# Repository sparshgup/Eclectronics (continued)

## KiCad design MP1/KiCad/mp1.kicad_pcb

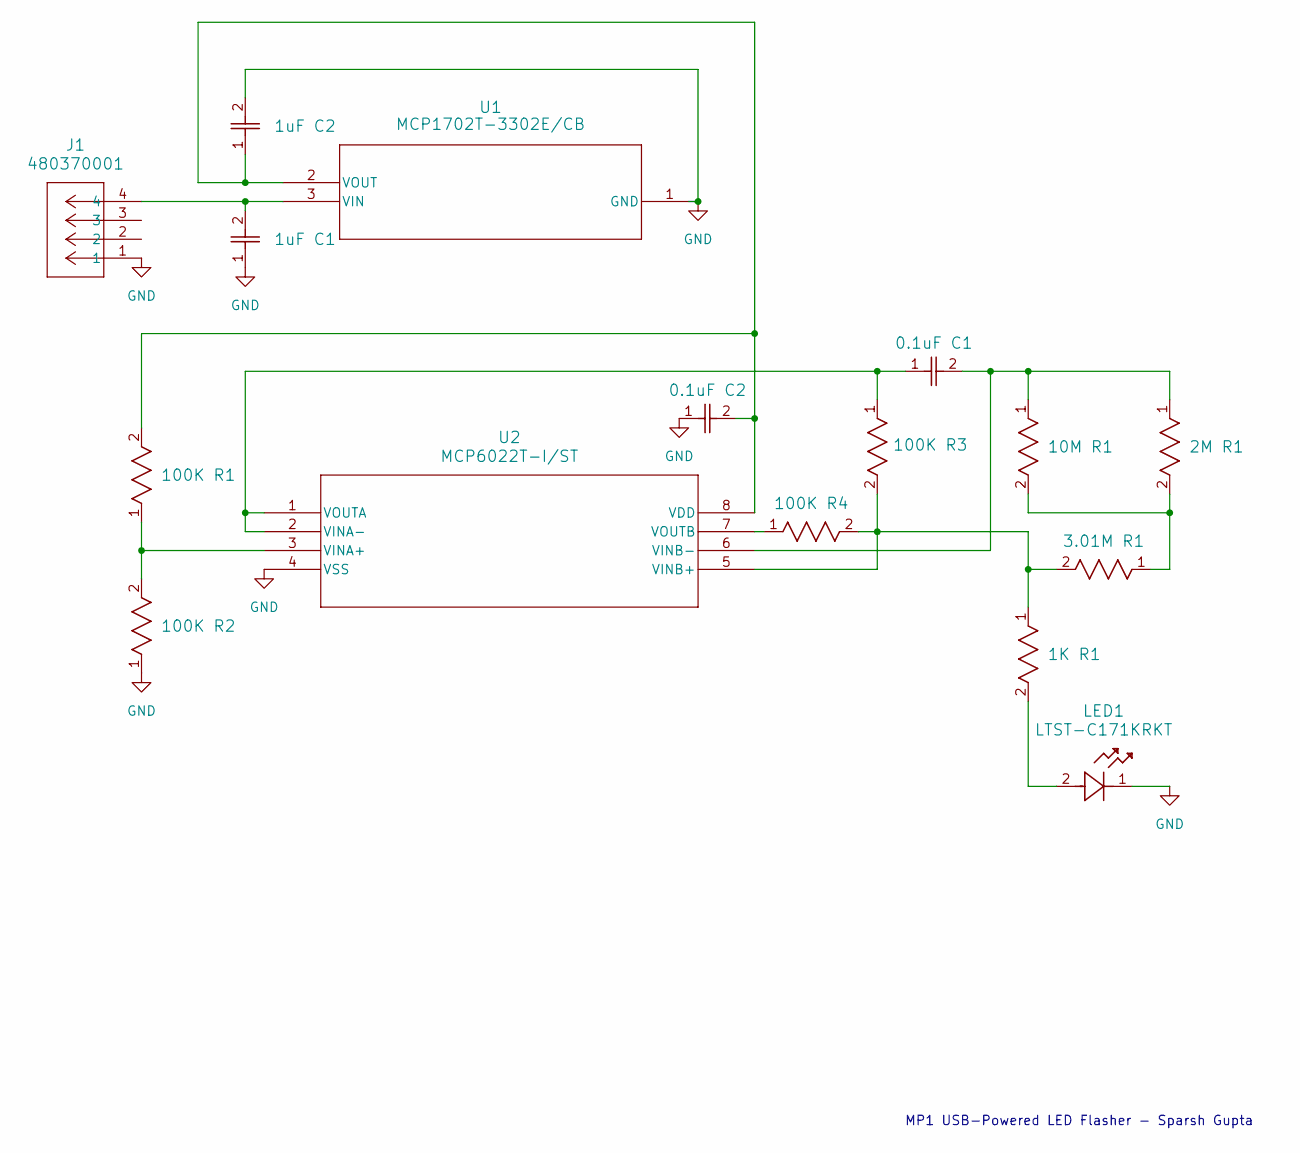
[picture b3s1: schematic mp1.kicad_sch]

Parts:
0.1uF C1, 0.1uF C2: CC0603JRX7R9BB104; CAP_CC0603_YAG
1K R1: RC0603FR-071KL; RC0603N_YAG
1uF C1, 1uF C2: C0603C105K3RACTU; CAPC17595_95N_KEM
2M R1: RC0603FR-072ML; RC0603N_YAG
3.01M R1: RC0603FR-073M01L; RC0603N_YAG
10M R1: RC0603FR-0710ML; RC0603N_YAG
100K R1, 100K R2, 100K R3, 100K R4: RC0603FR-07100KL; RC0603N_YAG
J1: 480370001; CONN_480370001_MOL
LED1: LTST-C171KRKT; LED_LTST-C171_LTO
U1: MCP1702T-3302E/CB; SOT-23A_MC_MCH
U2: MCP6022T-I/ST; TSSOP8_MC_MCH

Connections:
GND: 0.1uF C2.1, 1uF C1.1, 1uF C2.2, 100K R2.1, J1.1, LED1.1, U1.1 (GND), U2.4 (VSS)
unnamed: 1K R1.2, LED1.2
unnamed: 2M R1.2, 3.01M R1.1, 10M R1.2
unnamed: 1uF C1.2, J1.4, U1.3 (VIN)
unnamed: 0.1uF C2.2, 1uF C2.1, 100K R1.2, U1.2 (VOUT), U2.8 (VDD)
unnamed: 100K R1.1, 100K R2.2, U2.3 (VINA+)
unnamed: 0.1uF C1.1, 100K R3.1, U2.1 (VOUTA), U2.2 (VINA-)
unnamed: 1K R1.1, 3.01M R1.2, 100K R3.2, 100K R4.2, U2.5 (VINB+)
unnamed: 0.1uF C1.2, 2M R1.1, 10M R1.1, U2.6 (VINB-)
unnamed: 100K R4.1, U2.7 (VOUTB)

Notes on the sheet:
MP1 USB-Powered LED Flasher - Sparsh Gupta

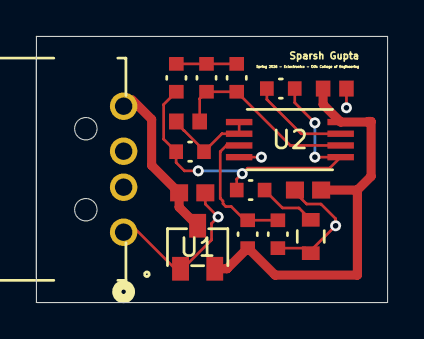
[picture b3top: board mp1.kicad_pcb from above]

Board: 2 copper layers, 19.5 x 14.8 mm, 16 parts (0 on the bottom side), 10 nets.

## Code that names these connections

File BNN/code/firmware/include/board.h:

#pragma once

// Pin map for the BNN board (matches the schematic).

#define PIN_UART_TX        0    // -> FPGA UART_RX (pin 25)
#define PIN_UART_RX        1    // <- FPGA UART_TX (pin 27)

#define PIN_SPI_SCK        2    // shared SPI bus: SCK to FPGA flash + FPGA pin 15
#define PIN_SPI_MOSI       3    // shared: MOSI / FPGA SI (flash DI + FPGA pin 17)
#define PIN_SPI_MISO       4    // shared: MISO / FPGA SO (flash DO + FPGA pin 14)
#define PIN_FPGA_CS        5    // FPGA pin 26 — data SPI CS (also doubles as SS during slave-SPI config)
#define PIN_FLASH_CS       6    // FPGA flash CS (also FPGA pin 16 — SPI_SS during slave-SPI config)
#define PIN_FPGA_CLK       7    // PWM out -> FPGA pin 35 (global buffer)

#define PIN_FPGA_CRESET    8    // -> FPGA CRESET_B (pin 8), active low
#define PIN_FPGA_CDONE     9    // <- FPGA CDONE (pin 7)

#define PIN_LED_R         10    // active low (RGB common anode)
#define PIN_LED_G         11
#define PIN_LED_B         12
#define PIN_USER_BTN      13    // active low, has external 10k pull-up

#define SPI_INST          spi0  // SPI0 owns GPIO2-5

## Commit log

2026-02-02 MP1 docs
2026-02-02 MP1 Kicad files
2026-02-23 Update README
    Added project details and images for USB-powered LED Flasher.
2026-02-26 Eclectronics MP3 lib files
2026-02-26 Update README with RP2350A
2026-02-26 Replace images in README for RP2350A
2026-03-06 update RP2350A board layout
2026-03-06 Update KiCad layout image in README
    Replaced the KiCad layout image link in README.md.
2026-03-06 update RP2350A
2026-03-06 Replace old KiCad layout image with a new one
2026-05-03 BNN files
2026-05-20 Add README for BNN
